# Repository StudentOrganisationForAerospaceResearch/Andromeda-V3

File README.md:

# Andromeda-V3
Flight Board with Daughter (Sensor) Board

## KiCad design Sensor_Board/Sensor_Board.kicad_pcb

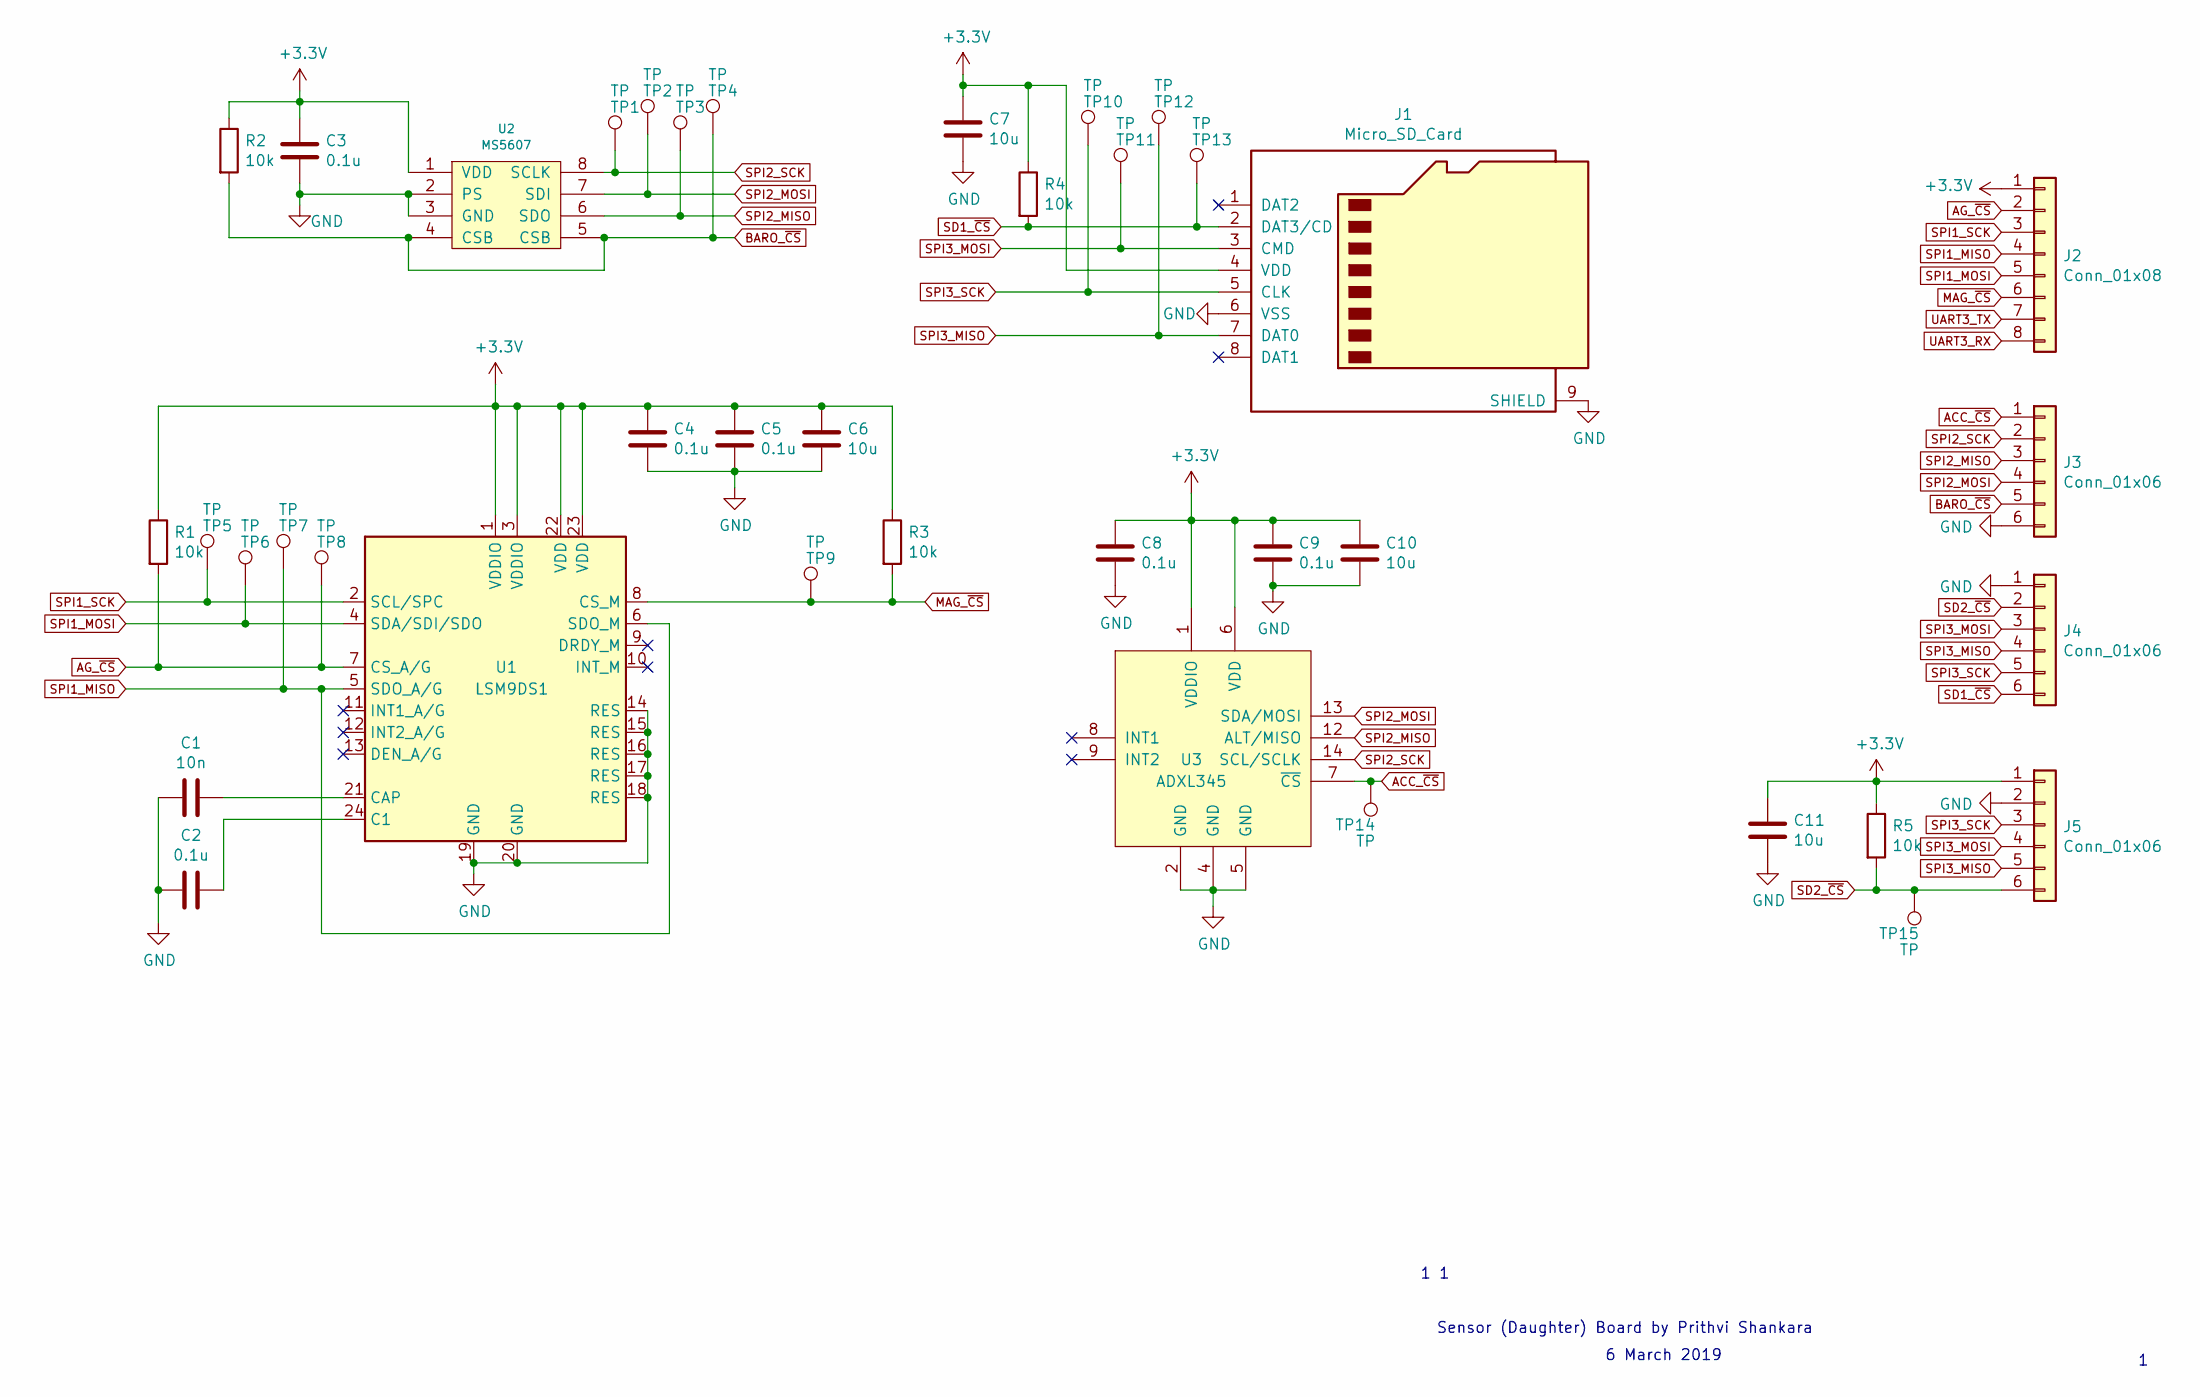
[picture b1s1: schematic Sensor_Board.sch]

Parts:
C1: 10n; C_0603
C2, C3, C4, C5, C8, C9: 0.1u; C_0603
C6, C7, C10, C11: 10u; C_0603
J1: Micro_SD_Card; SF-MICRO-SD
J2: Conn_01x08; PinHeader_1x08_P2.54mm_Vertical
J3, J4: Conn_01x06; PinHeader_1x06_P2.54mm_Vertical
J5: Conn_01x06; Molex_Micro-Fit_3.0_43045-0600_2x03_P3.00mm_Horizontal
R1, R2, R3, R4, R5: 10k; R_0603
TP1, TP2, TP3, TP4, TP5, TP6, TP7, TP8, TP9, TP10, TP11, TP12, TP13, TP14, TP15: TP; TestPoint_Pad_D1.5mm
U1: LSM9DS1; LGA-24L_3x3.5mm_Pitch0.43mm
U2: MS5607; LGA-8_3x5mm_Pitch1.25mm
U3: ADXL345; LGA-14_3x5mm_P0.8mm_LayoutBorder1x6y

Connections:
+3V3: C3.1, C4.1, C5.1, C6.1, C7.1, C8.1, C9.1, C10.1, C11.1, J1.4 (VDD), J2.1, J5.1, R1.1, R2.1, R3.1, R4.1, R5.1, U1.1 (VDDIO), U1.3 (VDDIO), U1.22 (VDD), U1.23 (VDD), U2.1 (VDD), U3.1 (VDDIO), U3.6 (VDD)
ACC_~CS: J3.1, TP14.1, U3.7 (~CS)
AG_~CS: J2.2, R1.2, TP8.1, U1.7 (CS_A/G)
BARO_~CS: J3.5, R2.2, TP4.1, U2.4 (CSB), U2.5 (CSB)
GND: C1.2, C2.2, C3.2, C4.2, C5.2, C6.2, C7.2, C8.2, C9.2, C10.2, C11.2, J1.6 (VSS), J1.9 (SHIELD), J3.6, J4.1, J5.2, U1.14 (RES), U1.15 (RES), U1.16 (RES), U1.17 (RES), U1.18 (RES), U1.19 (GND), U1.20 (GND), U2.2 (PS), U2.3 (GND), U3.2 (GND), U3.4 (GND), U3.5 (GND)
MAG_~CS: J2.6, R3.2, TP9.1, U1.8 (CS_M)
unnamed: C1.1, U1.21 (CAP)
unnamed: C2.1, U1.24 (C1)
SD1_~CS: J1.2 (DAT3/CD), J4.6, R4.2, TP13.1
SD2_~CS: J4.2, J5.6, R5.2, TP15.1
SPI1_MISO: J2.4, TP7.1, U1.5 (SDO_A/G), U1.6 (SDO_M)
SPI1_MOSI: J2.5, TP6.1, U1.4 (SDA/SDI/SDO)
SPI1_SCK: J2.3, TP5.1, U1.2 (SCL/SPC)
SPI2_MISO: J3.3, TP3.1, U2.6 (SDO), U3.12 (ALT/MISO)
SPI2_MOSI: J3.4, TP2.1, U2.7 (SDI), U3.13 (SDA/MOSI)
SPI2_SCK: J3.2, TP1.1, U2.8 (SCLK), U3.14 (SCL/SCLK)
SPI3_MISO: J1.7 (DAT0), J4.4, J5.5, TP12.1
SPI3_MOSI: J1.3 (CMD), J4.3, J5.4, TP11.1
SPI3_SCK: J1.5 (CLK), J4.5, J5.3, TP10.1
UART3_RX: J2.8
UART3_TX: J2.7

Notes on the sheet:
1 1
Sensor (Daughter) Board by Prithvi Shankara
6 March 2019

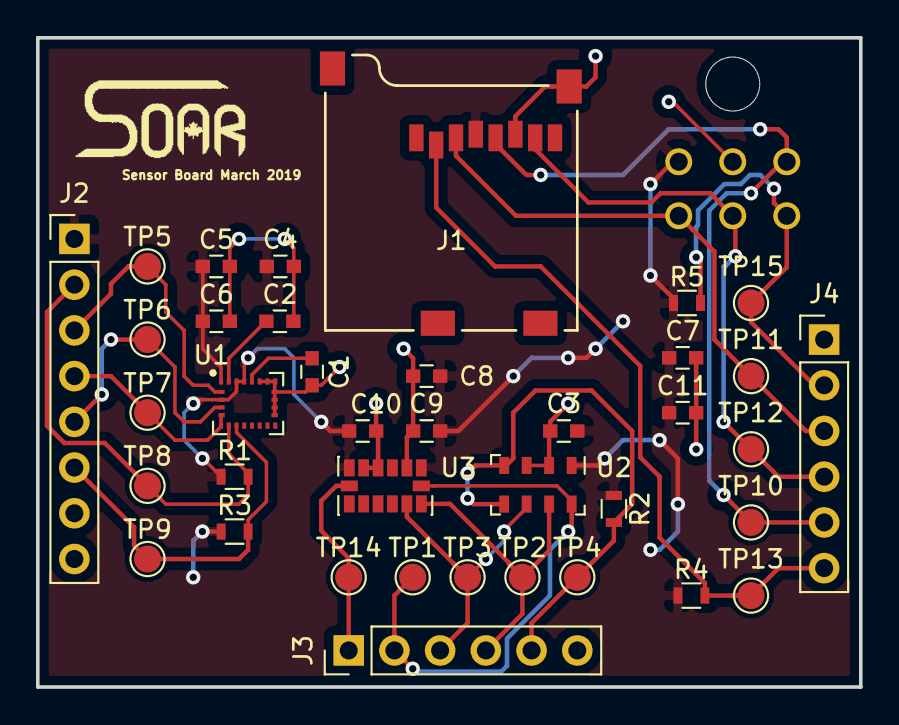
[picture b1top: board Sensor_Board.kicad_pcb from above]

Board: 2 copper layers, 45.7 x 36.1 mm, 40 parts (0 on the bottom side), 19 nets.

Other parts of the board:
LOGO_SOAR: LOGO_SOAR

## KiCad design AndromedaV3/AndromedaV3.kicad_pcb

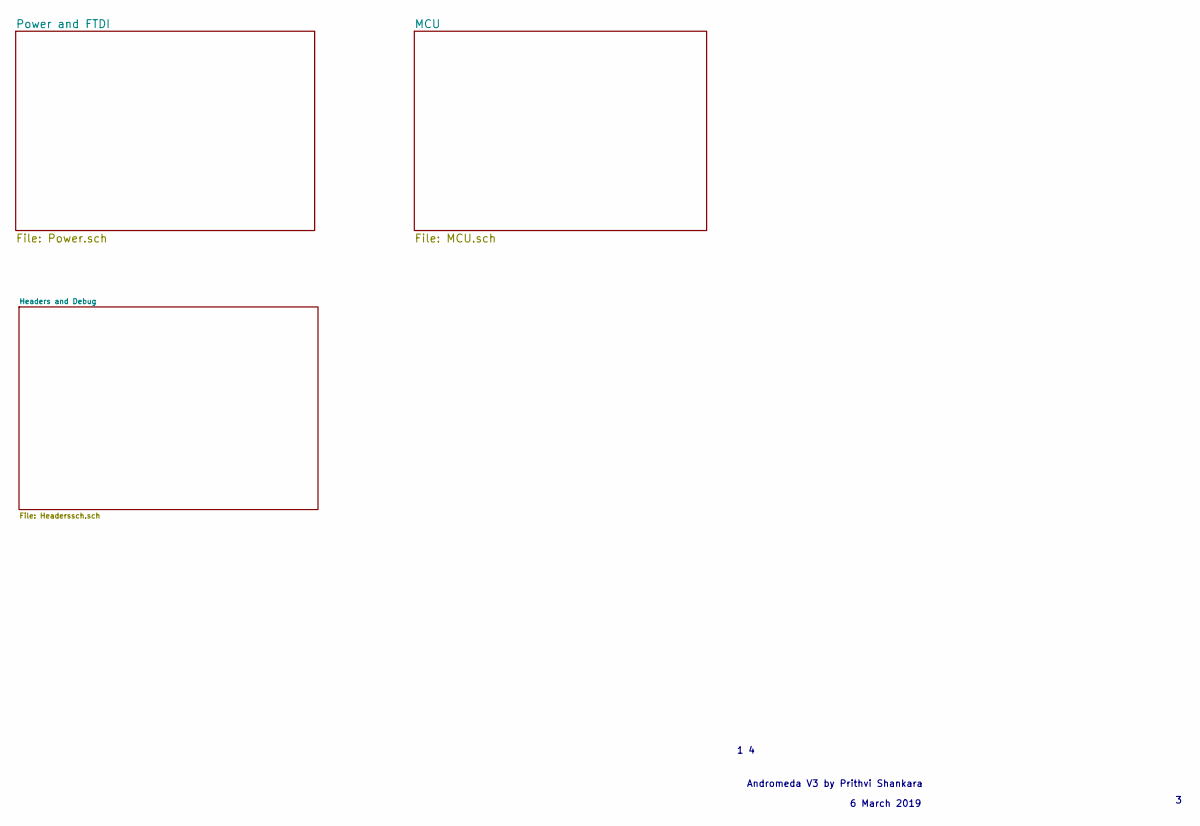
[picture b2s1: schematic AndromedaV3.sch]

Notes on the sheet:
1 4
Andromeda V3 by Prithvi Shankara
6 March 2019

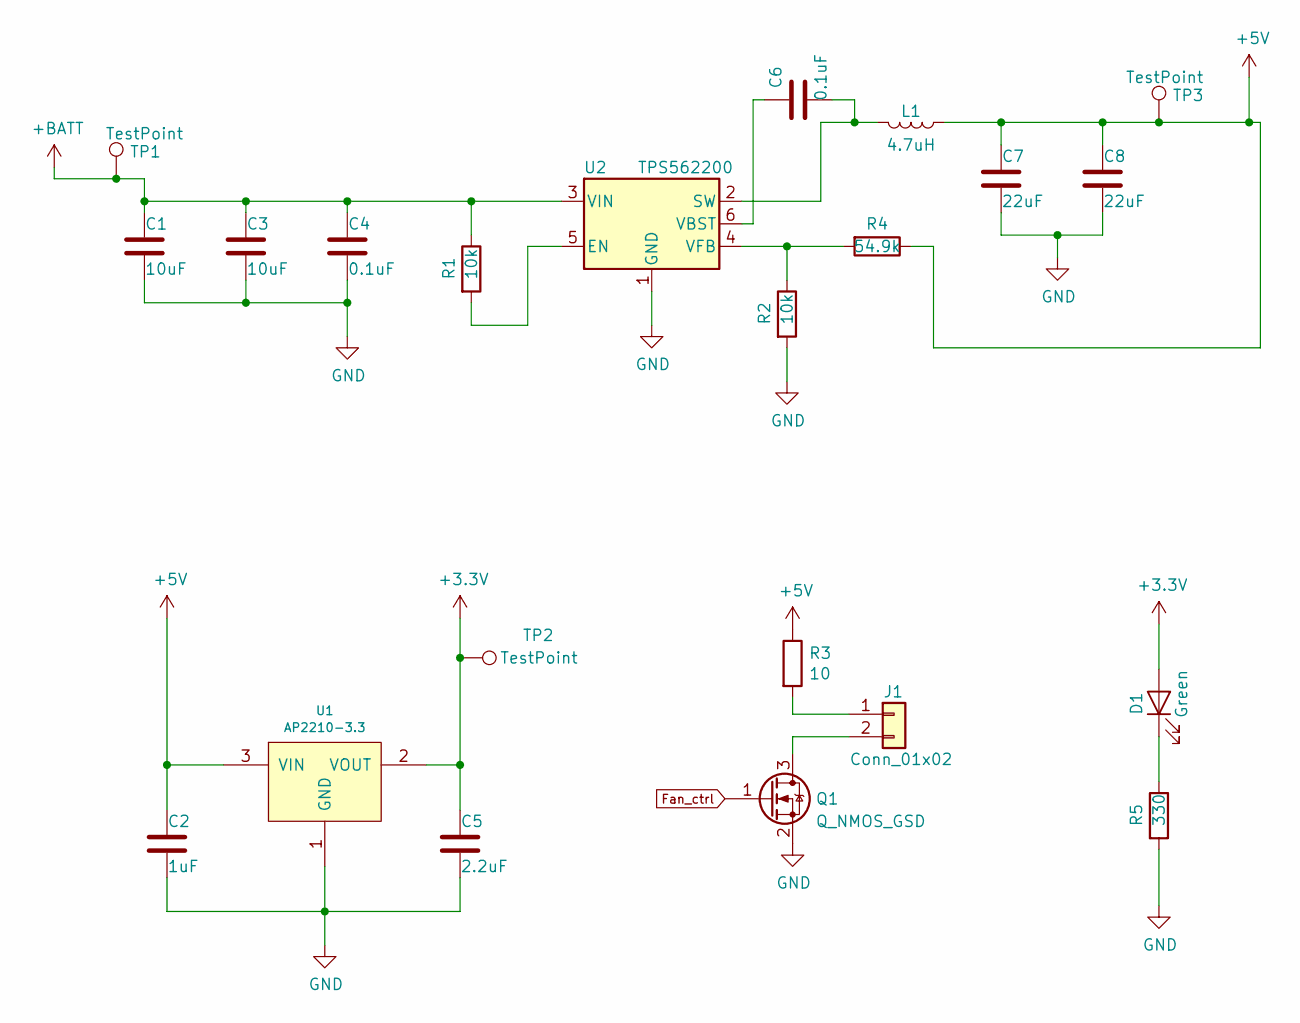
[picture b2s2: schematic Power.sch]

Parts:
C1, C3: 10uF; C_0603
C2: 1uF; C_0603
C4, C6: 0.1uF; C_0603
C5: 2.2uF; C_0603
C7, C8: 22uF; C_0603
D1: Green; LED_0805
J1: Conn_01x02; TerminalBlock_5mm_2POS_ED2600
L1: 4.7uH; L_1008
Q1: Q_NMOS_GSD; SOT-23
R1, R2: 10k; R_0603
R3: 10; R_0603
R4: 54.9k; R_0603
R5: 330; R_0603
TP1, TP2, TP3: TestPoint; TestPoint_Pad_D1.5mm
U1: AP2210-3.3; SOT-23
U2: TPS562200; SOT-23-6

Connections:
+3V3: C5.1, D1.2 (A), TP2.1, U1.2 (VOUT); also elsewhere on the board
+5V: C2.1, C7.1, C8.1, L1.1, R3.1, R4.1, TP3.1, U1.3 (VIN); also elsewhere on the board
+BATT: C1.1, C3.1, C4.1, R1.1, TP1.1, U2.3 (VIN); also elsewhere on the board
Fan_ctrl: Q1.1 (G); also elsewhere on the board
GND: C1.2, C2.2, C3.2, C4.2, C5.2, C7.2, C8.2, Q1.2 (S), R2.2, R5.2, U1.1 (GND), U2.1 (GND); also elsewhere on the board
unnamed: C6.1, L1.2, U2.2 (SW)
unnamed: C6.2, U2.6 (VBST)
unnamed: D1.1 (K), R5.1
unnamed: J1.1, R3.2
unnamed: J1.2, Q1.3 (D)
unnamed: R1.2, U2.5 (EN)
unnamed: R2.1, R4.2, U2.4 (VFB)

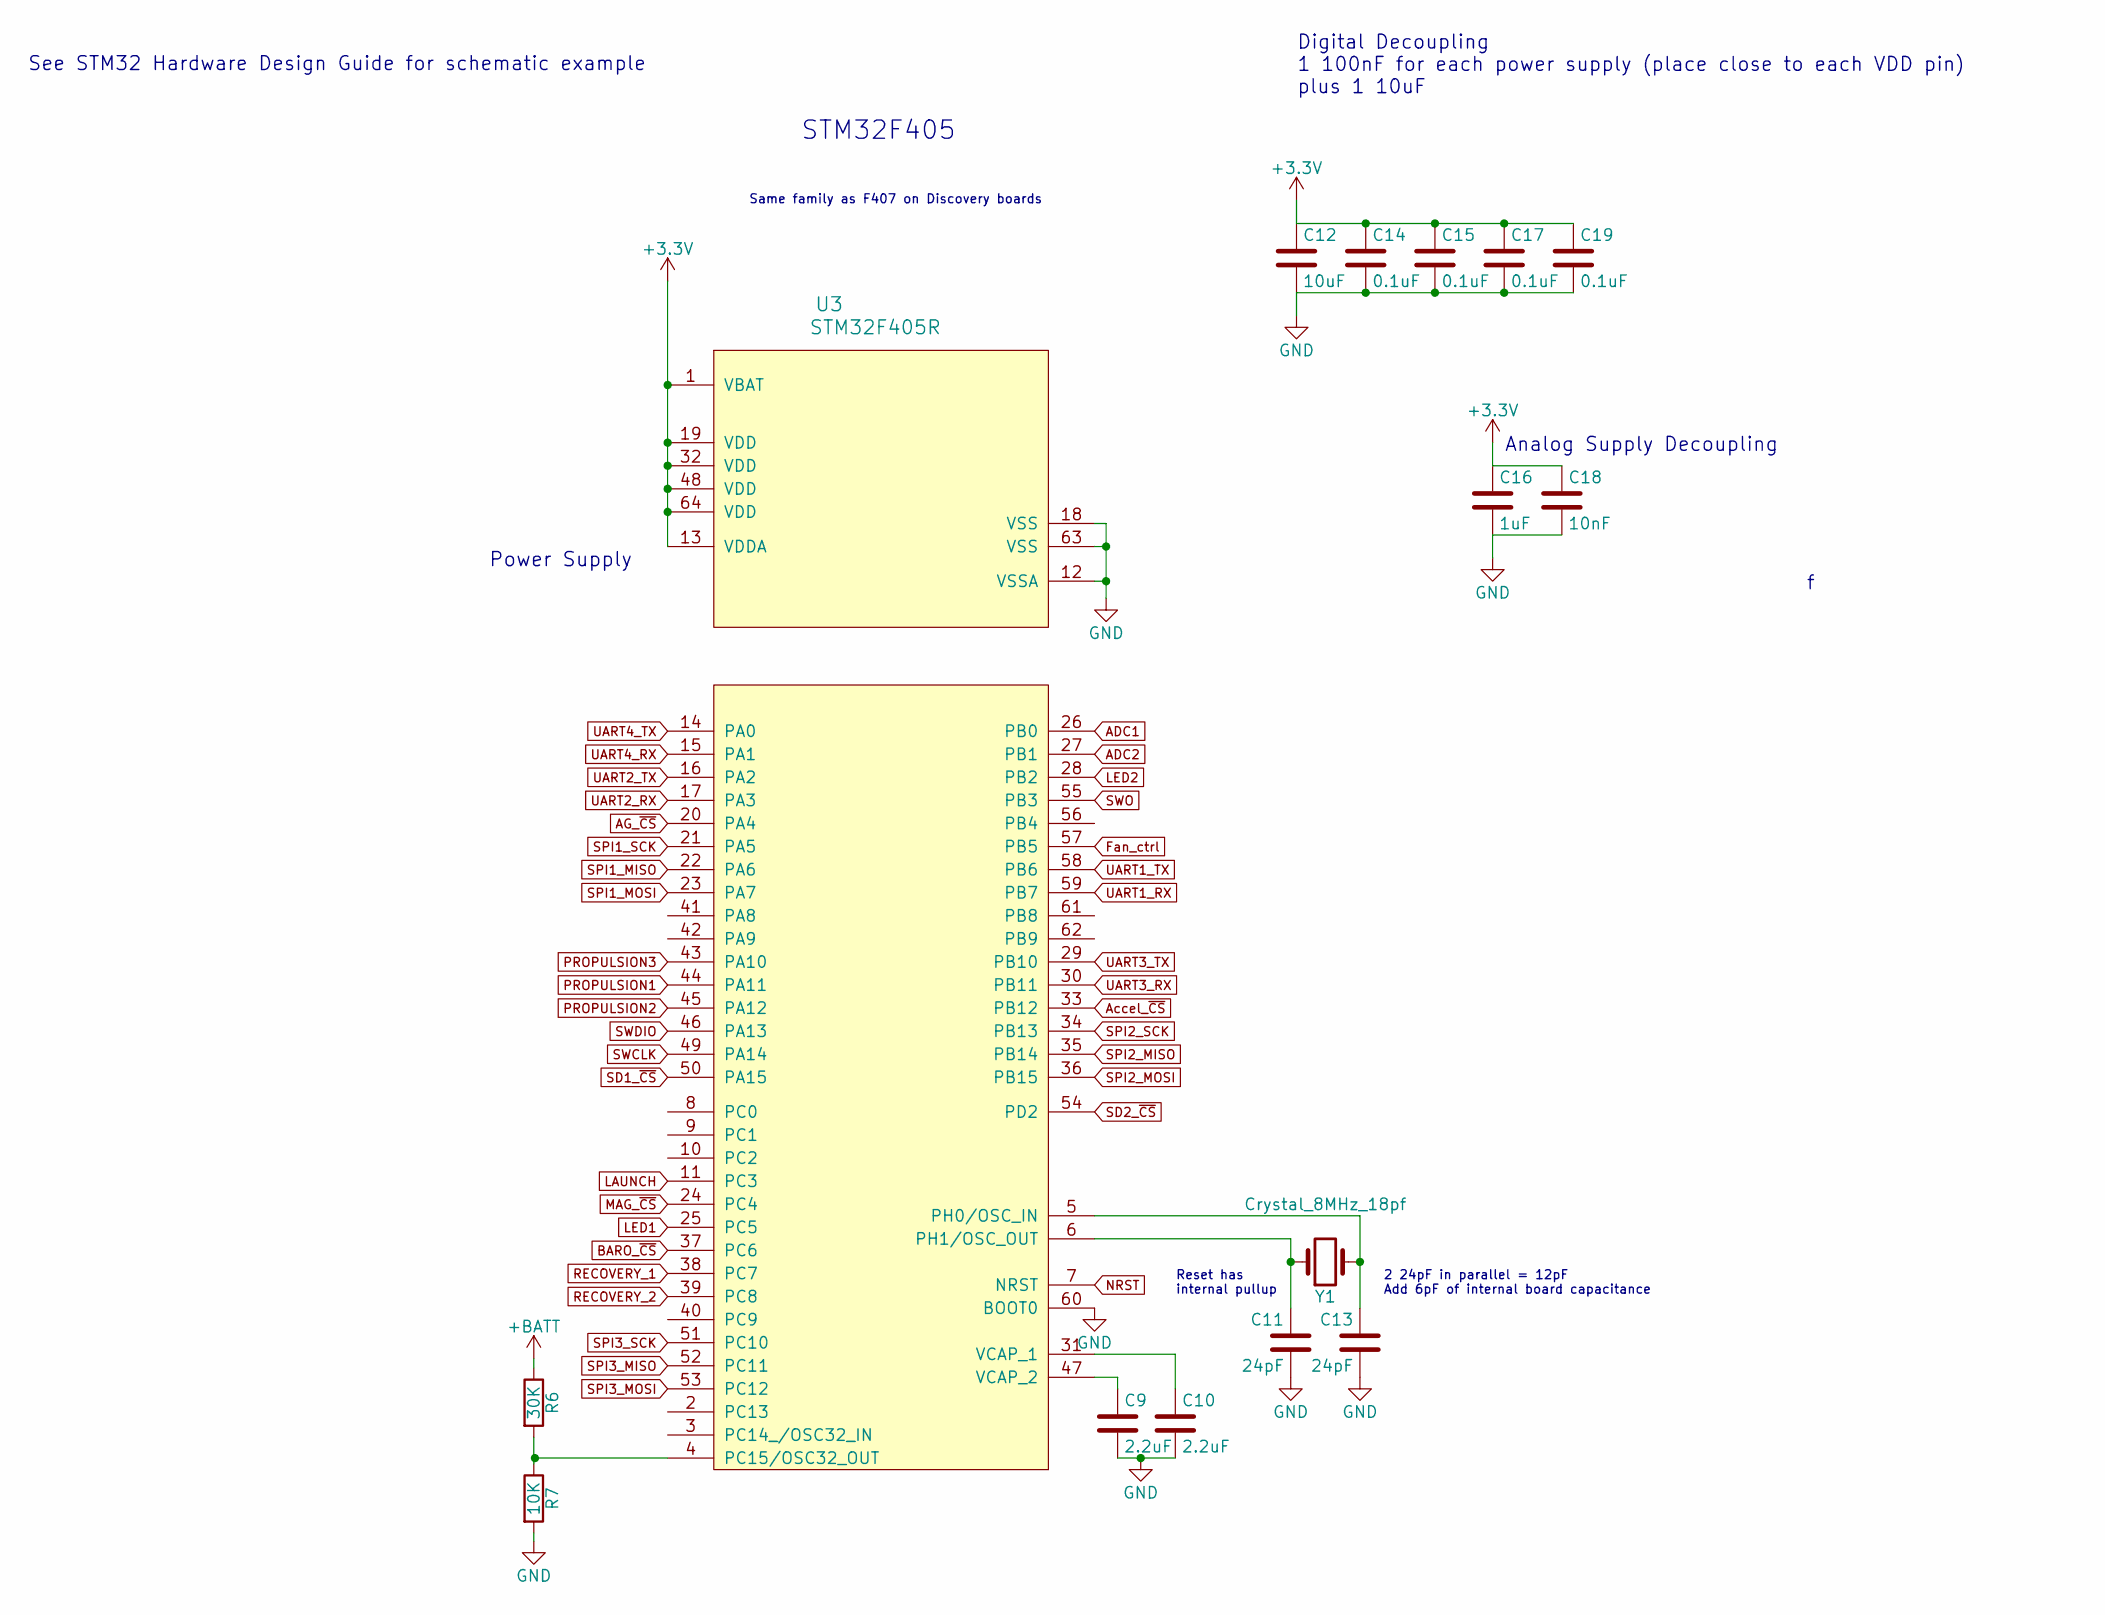
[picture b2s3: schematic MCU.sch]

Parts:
C9, C10: 2.2uF; C_0603
C11, C13: 24pF; C_0603
C12: 10uF; C_0603
C14, C15, C17, C19: 0.1uF; C_0603
C16: 1uF; C_0603
C18: 10nF; C_0603
R6: 30K; R_0603
R7: 10K; R_0603
U3: STM32F405R; LQFP-64_10x10mm_Pitch0.5mm; Digikey 497-11767-ND
Y1: Crystal_8MHz_18pf; Crystal_SMD_HC49-SD; Digikey 535-9089-1-ND

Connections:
+3V3: C12.1, C14.1, C15.1, C16.1, C17.1, C18.1, C19.1, U3.1 (VBAT), U3.13 (VDDA), U3.19 (VDD), U3.32 (VDD), U3.48 (VDD), U3.64 (VDD); also elsewhere on the board
+BATT: R6.1; also elsewhere on the board
ADC1: U3.26 (PB0); also elsewhere on the board
ADC2: U3.27 (PB1); also elsewhere on the board
AG_~CS: U3.20 (PA4); also elsewhere on the board
Accel_~CS: U3.33 (PB12); also elsewhere on the board
BARO_~CS: U3.37 (PC6); also elsewhere on the board
Fan_ctrl: U3.57 (PB5); also elsewhere on the board
GND: C9.2, C10.2, C11.2, C12.2, C13.2, C14.2, C15.2, C16.2, C17.2, C18.2, C19.2, R7.2, U3.12 (VSSA), U3.18 (VSS), U3.60 (BOOT0), U3.63 (VSS); also elsewhere on the board
LAUNCH: U3.11 (PC3); also elsewhere on the board
LED1: U3.25 (PC5); also elsewhere on the board
LED2: U3.28 (PB2); also elsewhere on the board
MAG_~CS: U3.24 (PC4); also elsewhere on the board
NRST: U3.7 (NRST); also elsewhere on the board
unnamed: C9.1, U3.47 (VCAP_2)
unnamed: C10.1, U3.31 (VCAP_1)
unnamed: C11.1, U3.6 (PH1/OSC_OUT), Y1.1
unnamed: C13.1, U3.5 (PH0/OSC_IN), Y1.2
unnamed: R6.2, R7.1, U3.4 (PC15/OSC32_OUT)
PROPULSION1: U3.44 (PA11); also elsewhere on the board
PROPULSION2: U3.45 (PA12); also elsewhere on the board
PROPULSION3: U3.43 (PA10); also elsewhere on the board
RECOVERY_1: U3.38 (PC7); also elsewhere on the board
RECOVERY_2: U3.39 (PC8); also elsewhere on the board
SD1_~CS: U3.50 (PA15); also elsewhere on the board
SD2_~CS: U3.54 (PD2); also elsewhere on the board
SPI1_MISO: U3.22 (PA6); also elsewhere on the board
SPI1_MOSI: U3.23 (PA7); also elsewhere on the board
SPI1_SCK: U3.21 (PA5); also elsewhere on the board
SPI2_MISO: U3.35 (PB14); also elsewhere on the board
SPI2_MOSI: U3.36 (PB15); also elsewhere on the board
SPI2_SCK: U3.34 (PB13); also elsewhere on the board
SPI3_MISO: U3.52 (PC11); also elsewhere on the board
SPI3_MOSI: U3.53 (PC12); also elsewhere on the board
SPI3_SCK: U3.51 (PC10); also elsewhere on the board
SWCLK: U3.49 (PA14); also elsewhere on the board
SWDIO: U3.46 (PA13); also elsewhere on the board
SWO: U3.55 (PB3); also elsewhere on the board
UART1_RX: U3.59 (PB7); also elsewhere on the board
UART1_TX: U3.58 (PB6); also elsewhere on the board
UART2_RX: U3.17 (PA3); also elsewhere on the board
UART2_TX: U3.16 (PA2); also elsewhere on the board
UART3_RX: U3.30 (PB11); also elsewhere on the board
UART3_TX: U3.29 (PB10); also elsewhere on the board
UART4_RX: U3.15 (PA1); also elsewhere on the board
UART4_TX: U3.14 (PA0); also elsewhere on the board

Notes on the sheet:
Reset has internal pullup
Digital Decoupling 1 100nF for each power supply (place close to each VDD pin) plus 1 10uF
Analog Supply Decoupling
See STM32 Hardware Design Guide for schematic example
Power Supply
2 24pF in parallel = 12pF Add 6pF of internal board capacitance
STM32F405
Same family as F407 on Discovery boards

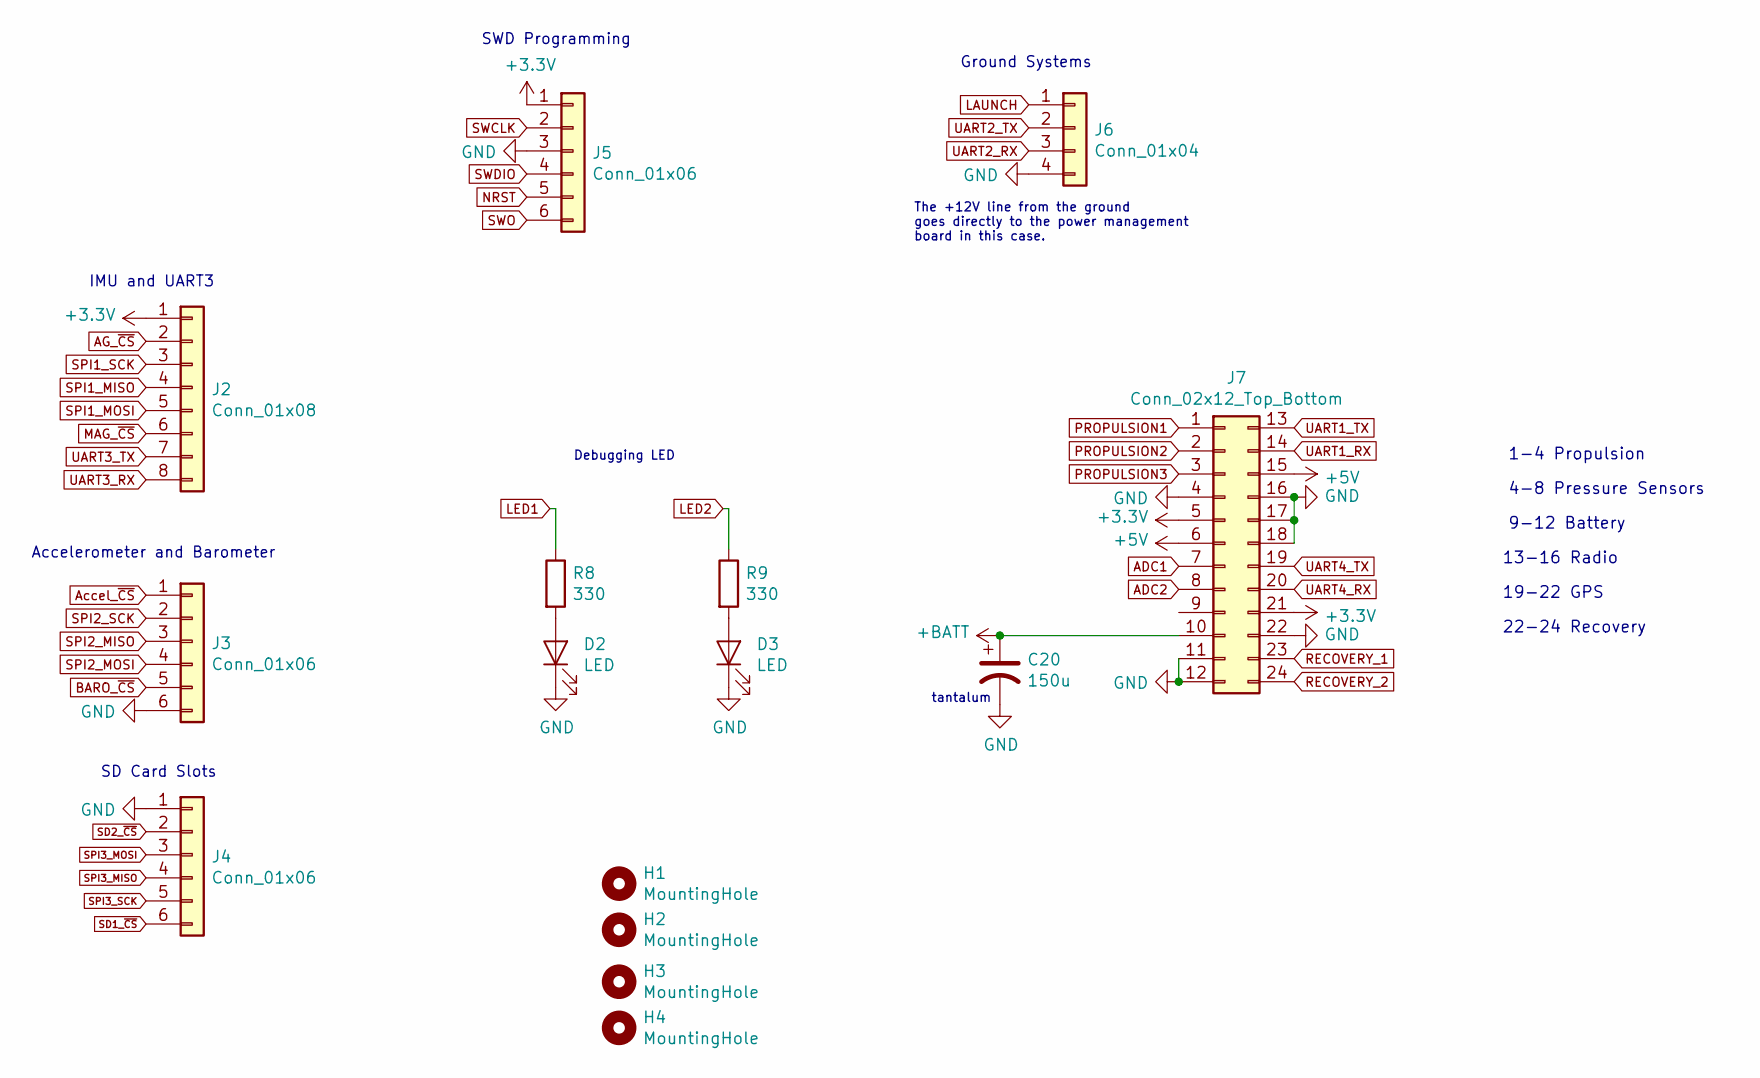
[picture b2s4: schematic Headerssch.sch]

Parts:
C20: 150u; CP_Tantalum_Case-D_EIA-7343-31_Reflow
D2, D3: LED; LED_0805
H1, H2, H3, H4: MountingHole; MountingHole_3.2mm_M3
J2: Conn_01x08; PinHeader_1x08_P2.54mm_Vertical
J3, J4, J5: Conn_01x06; PinHeader_1x06_P2.54mm_Vertical
J6: Conn_01x04; Molex_Micro-Fit_3.0_43045-0400_2x02_P3.00mm_Horizontal
J7: Conn_02x12_Top_Bottom; Pin_Header_Straight_2x12_Pitch2.54mm
R8, R9: 330; R_0603

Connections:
+3V3: J2.1, J5.1, J7.5, J7.21; also elsewhere on the board
+5V: J7.6, J7.15; also elsewhere on the board
+BATT: C20.1, J7.10; also elsewhere on the board
ADC1: J7.7; also elsewhere on the board
ADC2: J7.8; also elsewhere on the board
AG_~CS: J2.2; also elsewhere on the board
Accel_~CS: J3.1; also elsewhere on the board
BARO_~CS: J3.5; also elsewhere on the board
GND: C20.2, D2.1 (K), D3.1 (K), J3.6, J4.1, J5.3, J6.4, J7.4, J7.11, J7.12, J7.16, J7.17, J7.18, J7.22; also elsewhere on the board
LAUNCH: J6.1; also elsewhere on the board
LED1: R8.1; also elsewhere on the board
LED2: R9.1; also elsewhere on the board
MAG_~CS: J2.6; also elsewhere on the board
NRST: J5.5; also elsewhere on the board
unnamed: D2.2 (A), R8.2
unnamed: D3.2 (A), R9.2
PROPULSION1: J7.1; also elsewhere on the board
PROPULSION2: J7.2; also elsewhere on the board
PROPULSION3: J7.3; also elsewhere on the board
RECOVERY_1: J7.23; also elsewhere on the board
RECOVERY_2: J7.24; also elsewhere on the board
SD1_~CS: J4.6; also elsewhere on the board
SD2_~CS: J4.2; also elsewhere on the board
SPI1_MISO: J2.4; also elsewhere on the board
SPI1_MOSI: J2.5; also elsewhere on the board
SPI1_SCK: J2.3; also elsewhere on the board
SPI2_MISO: J3.3; also elsewhere on the board
SPI2_MOSI: J3.4; also elsewhere on the board
SPI2_SCK: J3.2; also elsewhere on the board
SPI3_MISO: J4.4; also elsewhere on the board
SPI3_MOSI: J4.3; also elsewhere on the board
SPI3_SCK: J4.5; also elsewhere on the board
SWCLK: J5.2; also elsewhere on the board
SWDIO: J5.4; also elsewhere on the board
SWO: J5.6; also elsewhere on the board
UART1_RX: J7.14; also elsewhere on the board
UART1_TX: J7.13; also elsewhere on the board
UART2_RX: J6.3; also elsewhere on the board
UART2_TX: J6.2; also elsewhere on the board
UART3_RX: J2.8; also elsewhere on the board
UART3_TX: J2.7; also elsewhere on the board
UART4_RX: J7.20; also elsewhere on the board
UART4_TX: J7.19; also elsewhere on the board

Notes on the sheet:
Debugging LED
SWD Programming
Ground Systems
tantalum
13-16 Radio
9-12 Battery
19-22 GPS
22-24 Recovery
1-4 Propulsion
4-8 Pressure Sensors
The +12V line from the ground goes directly to the power management board in this case.
IMU and UART3
Accelerometer and Barometer
SD Card Slots

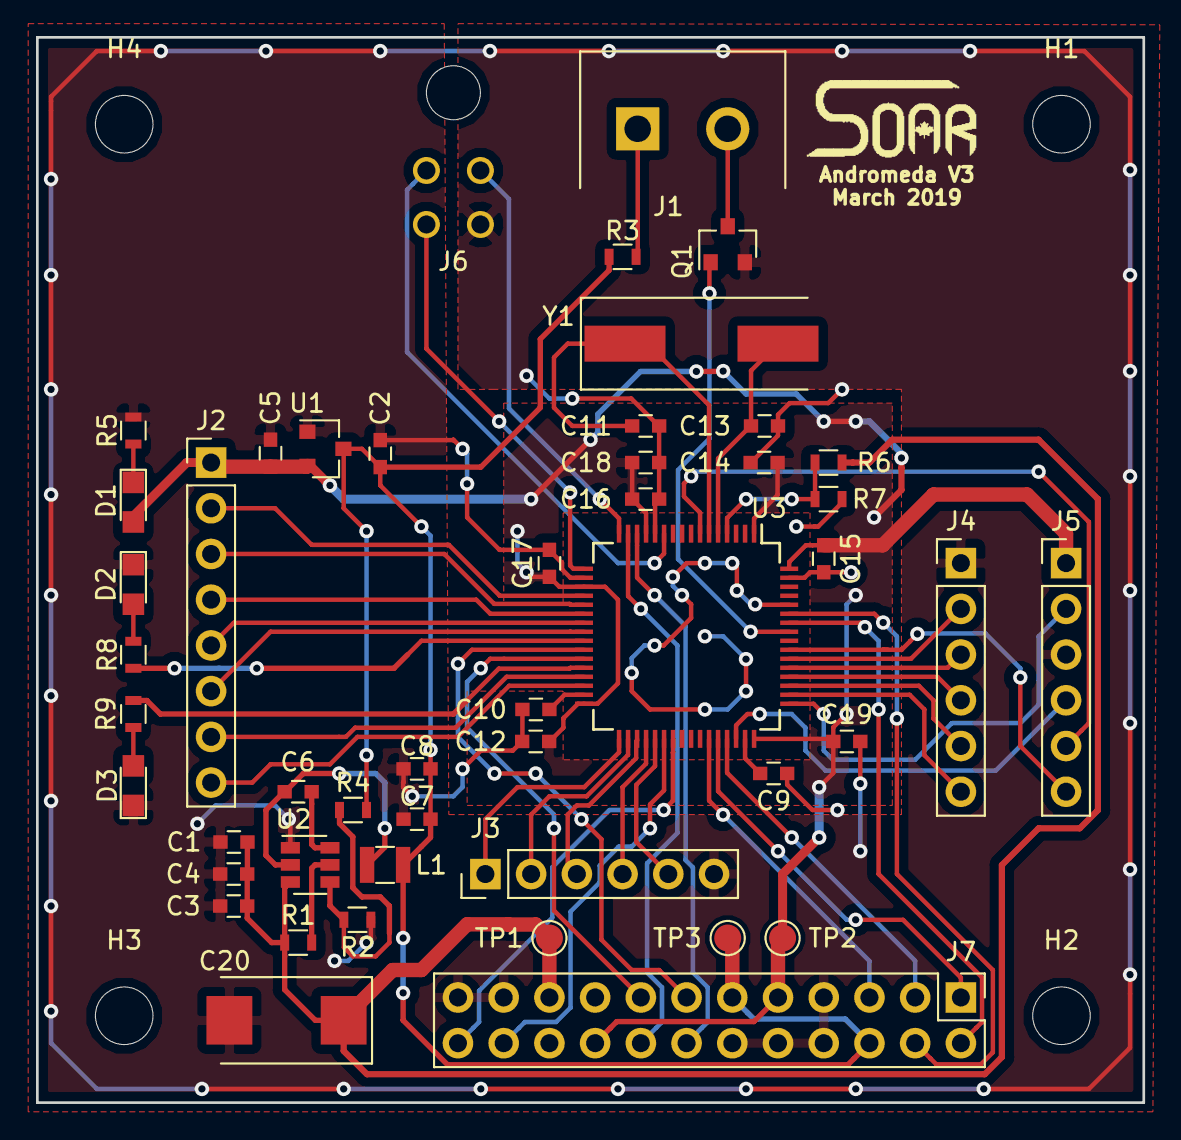
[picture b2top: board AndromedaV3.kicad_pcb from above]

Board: 2 copper layers, 61.5 x 59.2 mm, 53 parts (0 on the bottom side), 56 nets.

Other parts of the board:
LOGO_SOAR: LOGO_SOAR
